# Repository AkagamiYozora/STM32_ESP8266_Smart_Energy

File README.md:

# STM32 ESP8266 Smart Energy Monitoring Over Telegram

Overview
===

The combination of STM32 and ESP8266 to monitor electrical energy used by house system.

Moreover, it could also detect back-ward current flow on neutral wire so that admin will be noticed if there was an exceptional current flowing through the system. As an IoT based project, this system also connected to Telegram using WiFi on ESP8266 as its base for easy control and monitor using smartphone.

Component used on this project:
1. STM32 F103C8T6
2. ESP8266
3. PZEM-004t
4. ACS712
5. LCD 16x2
6. I2C
7. MicroSD Module
8. GPS Neo 6M-V2

Source and documentation will be updated along with this project.

Ringkasan
===

Penggunaan STM32 dan ESP8266 untuk monitoring energi yang digunakan oleh sistem kelistrikan di rumah.

Selain dari fungs utamanya, prototipe in juga mampu mendeteksi arus balik pada kabel netral sehingga admin akan mendapatkan informasi jika terjadi arus yang mengalir secara tidak wajar pada sistem. Sebagai project IoT, sistem ini juga terhubung dengan Telegram melalui WiFi pada ESP8266 sebagai basis kontrol serta monitoringnya menggunakan ponsel.

Komponen yang digunakan pada proyek ini:
1. STM32 F103C8T6
2. ESP8266
3. PZEM-004t
4. ACS712
5. LCD 16x2
6. I2C
7. MicroSD Module
8. GPS Neo 6M-V2

Sumber serta dokumentasi akan diupdate bersamaan dengan berjalannya proyek ini.

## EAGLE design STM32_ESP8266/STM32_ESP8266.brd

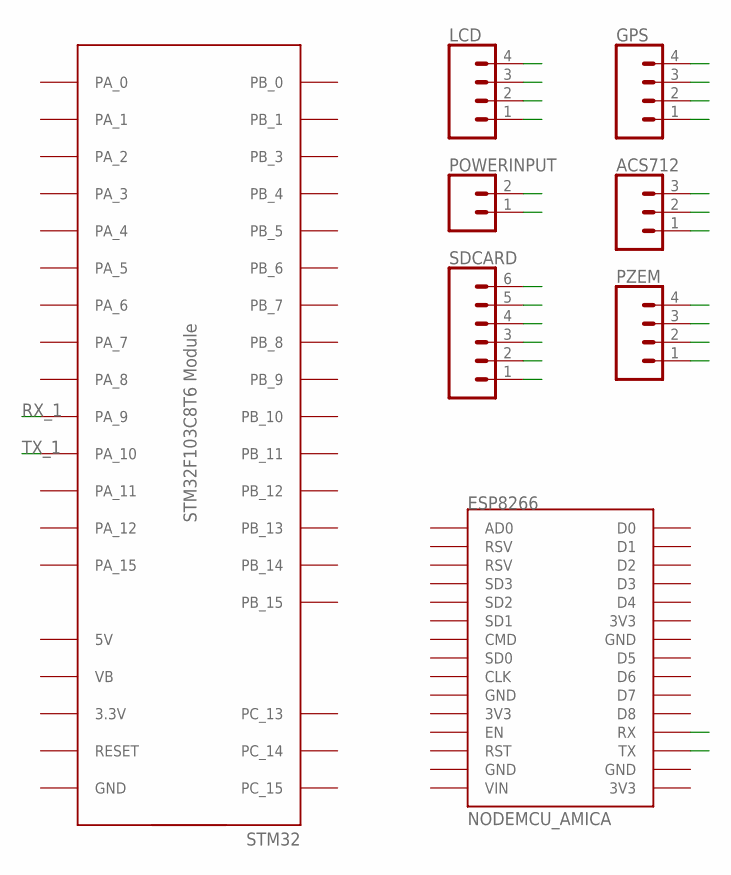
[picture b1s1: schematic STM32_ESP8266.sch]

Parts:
ACS712: 455-1750-1-ND; 1X03
ESP8266: NODEMCU_AMICA
GPS: CONN_04PTH; 1X04
LCD: CONN_04PTH; 1X04
POWERINPUT: CONN_02; 1X02
PZEM: CONN_04PTH; 1X04
SDCARD: CONN_06SILK_FEMALE_PTH; 1X06
STM32: STM32F103C8T6-MODULE

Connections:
RX_1: ESP8266.RX, STM32.PA_9
TX_1: ESP8266.TX, STM32.PA_10

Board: 2 copper layers, 8 parts (0 on the bottom side), 2 nets, no tracks yet.

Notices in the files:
parts and their libraries:
SparkFun-Connectors: Licensing: Creative Commons ShareAlike 4.0 International - https://creativecommons.org/licenses/by-sa/4.0
